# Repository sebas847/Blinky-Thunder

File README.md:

# Blinky-Thunder
This project is fairly simple but interesting to do. It involves LEDs (which blink) attached to a PCB shaped like a thunderclap. It has two main microcontrollers: the NE555P and CD4017, as well as resistors for the LEDs and two capacitors.
I decided to do this project because I realized that it wasn't very complicated to do and it would teach me new things, such as designs and slightly more complicated logic of schemes, as well as routing with an irregular shape.
Here are some images of the electronic schematic, PCB design, and 3D PCB layout for both layers.

And finally, here is the Bill of Materials (BOM) of all the components included in the project.

PCB: Custom lightning-bolt shaped board — $4.00 (1 unit)

NE555P: Precision Timer IC (Clock pulse generator) — $0.50 (1 unit)

CD4017: Decade Counter IC (LED sequencer) — $0.60 (1 unit)

LEDs (Red): 5mm Light Emitting Diodes — $1.00 (10 units)

Potentiometer: Variable Resistor for speed control — $0.80 (1 unit)

Resistors: Current limiting and circuit configuration — $0.25 (5 units)

Capacitors: Timing and power decoupling — $0.30 (2 units)

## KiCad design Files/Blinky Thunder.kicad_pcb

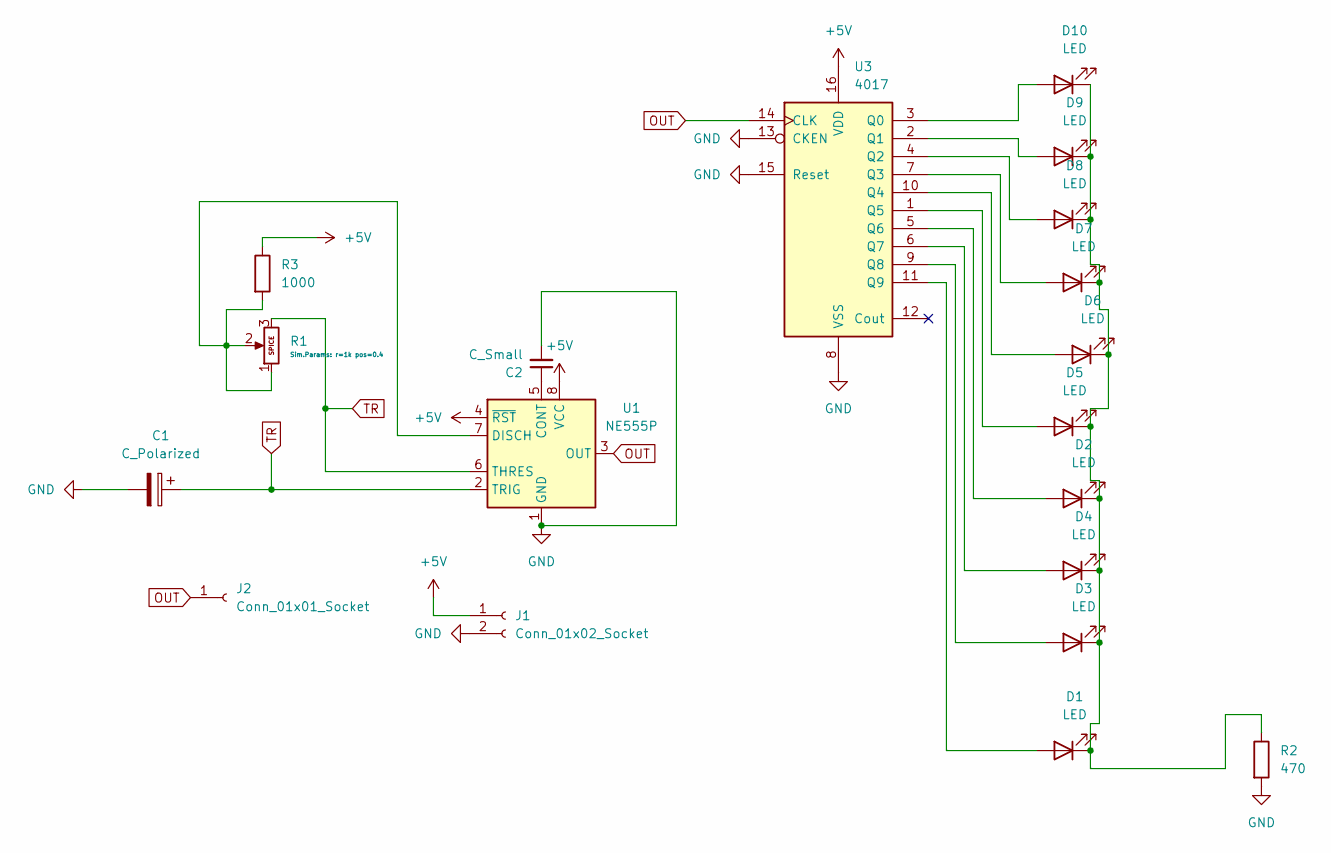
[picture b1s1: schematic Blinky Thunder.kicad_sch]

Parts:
C1: C_Polarized; CP_Radial_D5.0mm_P2.00mm
C2: C_Small; C_Disc_D3.0mm_W1.6mm_P2.50mm
D1, D2, D3, D4, D5, D6, D7, D8, D9, D10: LED; LED_D5.0mm
J1: Conn_01x02_Socket; PinHeader_1x02_P2.54mm_Vertical
J2: Conn_01x01_Socket; PinHeader_1x01_P2.54mm_Vertical
R1: Potentiometer; Potentiometer_Bourns_PTV09A-1_Single_Vertical
R2: 470; R_Axial_DIN0207_L6.3mm_D2.5mm_P7.62mm_Horizontal
R3: 1000; R_Axial_DIN0207_L6.3mm_D2.5mm_P7.62mm_Horizontal
U1: NE555P; DIP-8_W7.62mm
U3: 4017; N16

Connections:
+5V: J1.1, R3.1, U1.4 (~RST), U1.8 (VCC), U3.16 (VDD)
GND: C1.2, C2.2, J1.2, R2.2, U1.1 (GND), U3.8 (VSS), U3.13 (CKEN), U3.15 (Reset)
unnamed: D1.2 (A), U3.11 (Q9)
unnamed: D1.1 (K), D2.1 (K), D3.1 (K), D4.1 (K), D5.1 (K), D6.1 (K), D7.1 (K), D8.1 (K), D9.1 (K), D10.1 (K), R2.1
unnamed: D2.2 (A), U3.5 (Q6)
unnamed: D3.2 (A), U3.9 (Q8)
unnamed: D4.2 (A), U3.6 (Q7)
unnamed: D5.2 (A), U3.1 (Q5)
unnamed: D6.2 (A), U3.10 (Q4)
unnamed: D7.2 (A), U3.7 (Q3)
unnamed: D8.2 (A), U3.4 (Q2)
unnamed: D9.2 (A), U3.2 (Q1)
unnamed: D10.2 (A), U3.3 (Q0)
unnamed: C2.1, U1.5 (CONT)
unnamed: R1.1, R1.2, R3.2, U1.7 (DISCH)
OUT: J2.1 (Pin_1_1), U1.3 (OUT), U3.14 (CLK)
TR: C1.1, R1.3, U1.2 (TRIG), U1.6 (THRES)

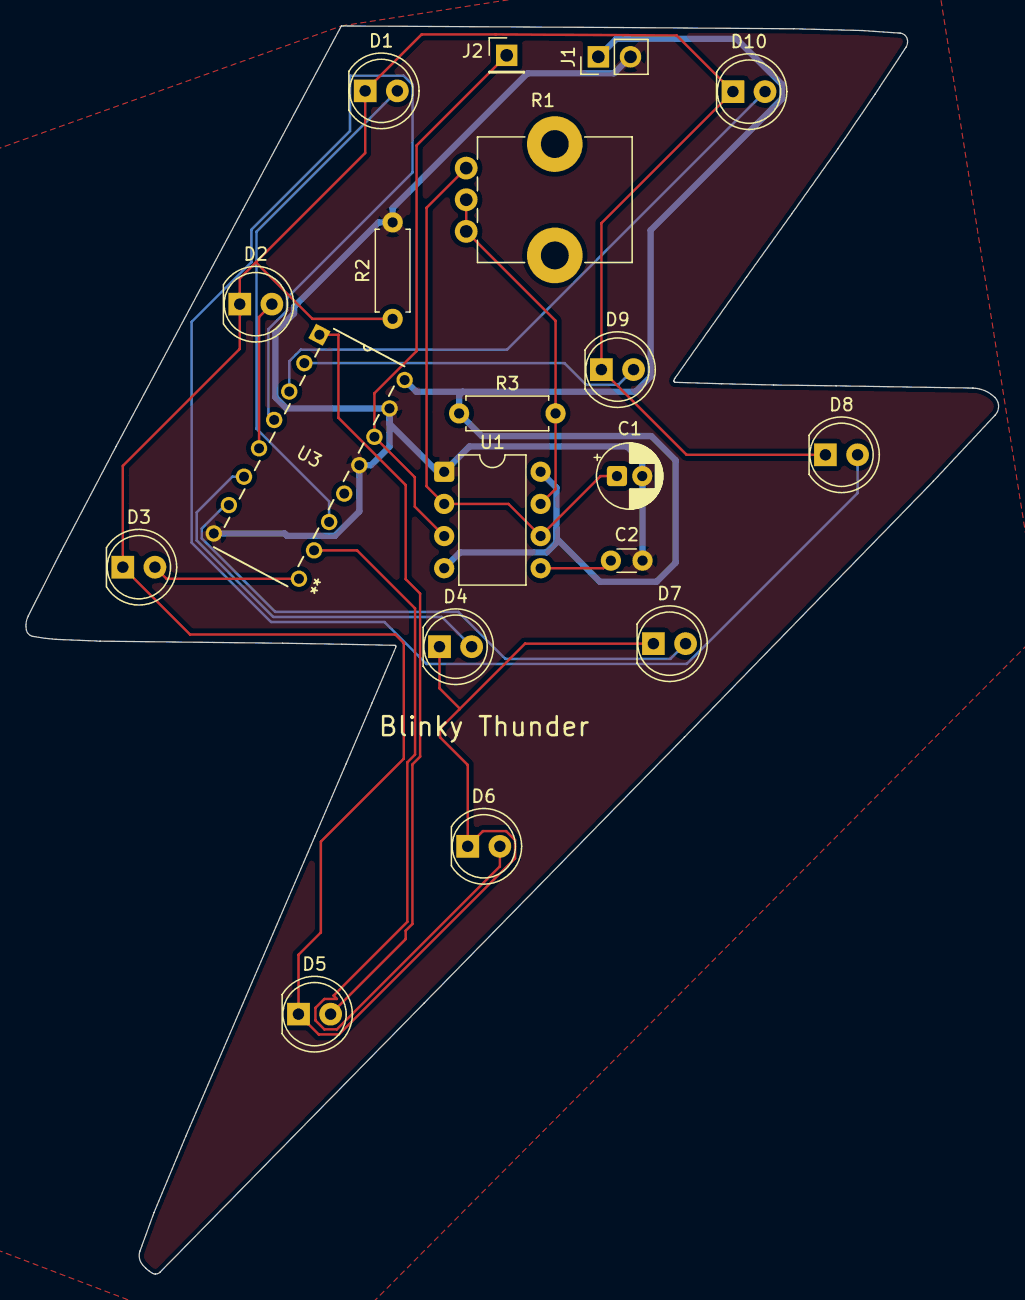
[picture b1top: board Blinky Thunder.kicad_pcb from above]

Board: 2 copper layers, 76.8 x 98.6 mm, 19 parts (0 on the bottom side), 17 nets.
